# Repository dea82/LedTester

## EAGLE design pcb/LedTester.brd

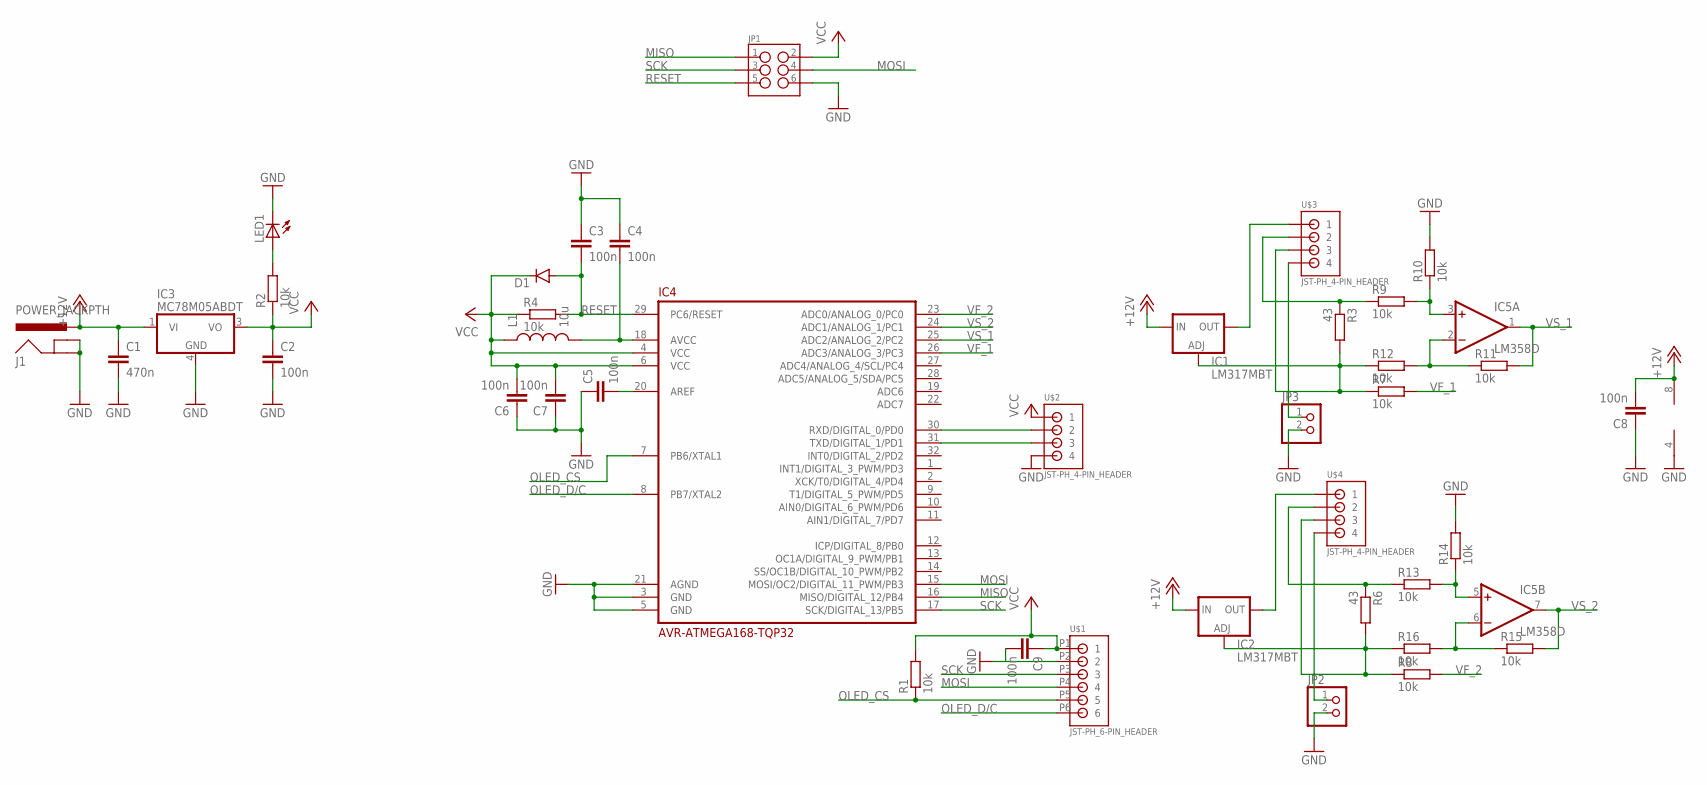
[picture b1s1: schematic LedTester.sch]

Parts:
C1: 470n; C0603
C2, C3, C4, C5, C6, C7, C8, C9: 100n; C0603
D1: DIODESOD; SOD-323
IC1, IC2: LM317MBT; TO220L1
IC3: MC78M05ABDT; DPACK_3
IC4: AVR-ATMEGA168-TQP32; QFP32
IC5: LM358D; SO08
J1: POWER_JACKPTH; POWER_JACK_PTH
JP1: M03X2SHROUD; 2X3-SHROUDED
JP2, JP3: PINHD-1X2; 1X02
L1: 10u; 0603
LED1: LEDCHIP-LED0603; CHIP-LED0603
R1, R2, R4, R7, R8, R9, R10, R11, R12, R13, R14, R15, R16: 10k; R0603
R3, R6: 43; R0603
U$1: JST-PH_6-PIN_HEADER; JST_B6B-PH_HEADER
U$2, U$3, U$4: JST-PH_4-PIN_HEADER; JST_B4B-PH_HEADER

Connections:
+12V: C1.1, C8.2, IC1.3 (IN), IC2.3 (IN), IC3.1 (VI), IC5.8 (V+), J1.PWR
GND: C1.2, C2.2, C3.1, C4.1, C5.1, C6.1, C7.1, C8.1, C9.2, IC3.4 (GND), IC4.3 (GND), IC4.5 (GND), IC4.21 (AGND), IC5.4 (V-), J1.GND, J1.GNDBREAK, JP1.6, JP2.2, JP3.2, LED1.C, R10.2, R14.2, U$1.P2 (2), U$2.P4 (4)
MISO: IC4.16 (MISO/DIGITAL_12/PB4), JP1.1
MOSI: IC4.15 (MOSI/OC2/DIGITAL_11_PWM/PB3), JP1.4, U$1.P4 (4)
unnamed: C5.2, IC4.20 (AREF)
unnamed: IC1.2 (OUT), U$3.P1 (1)
unnamed: C4.2, IC4.18 (AVCC), L1.2
unnamed: R3.1, R9.1, U$3.P2 (2)
unnamed: IC1.1 (ADJ), R3.2, R7.1, R12.1, U$3.P3 (3)
unnamed: IC2.2 (OUT), U$4.P1 (1)
unnamed: R6.1, R13.1, U$4.P2 (2)
unnamed: IC2.1 (ADJ), R6.2, R8.1, R16.1, U$4.P3 (3)
unnamed: LED1.A, R2.2
unnamed: IC4.30 (RXD/DIGITAL_0/PD0), U$2.P2 (2)
unnamed: IC4.31 (TXD/DIGITAL_1/PD1), U$2.P3 (3)
unnamed: IC5.2 (-IN), R11.1, R12.2
unnamed: IC5.3 (+IN), R9.2, R10.1
unnamed: IC5.6 (-IN), R15.1, R16.2
unnamed: IC5.5 (+IN), R13.2, R14.1
unnamed: JP3.1, U$3.P4 (4)
unnamed: JP2.1, U$4.P4 (4)
OLED_CS: IC4.7 (PB6/XTAL1), R1.1, U$1.P5 (5)
OLED_D/C: IC4.8 (PB7/XTAL2), U$1.P6 (6)
RESET: C3.2, D1.A, IC4.29 (PC6/RESET), JP1.5, R4.2
SCK: IC4.17 (SCK/DIGITAL_13/PB5), JP1.3, U$1.P3 (3)
VCC: C2.1, C6.2, C7.2, C9.1, D1.C, IC3.3 (VO), IC4.4 (VCC), IC4.6 (VCC), JP1.2, L1.1, R1.2, R2.1, R4.1, U$1.P1 (1), U$2.P1 (1)
VF_1: IC4.26 (ADC3/ANALOG_3/PC3), R7.2
VF_2: IC4.23 (ADC0/ANALOG_0/PC0), R8.2
VS_1: IC4.25 (ADC2/ANALOG_2/PC2), IC5.1 (OUT), R11.2
VS_2: IC4.24 (ADC1/ANALOG_1/PC1), IC5.7 (OUT), R15.2

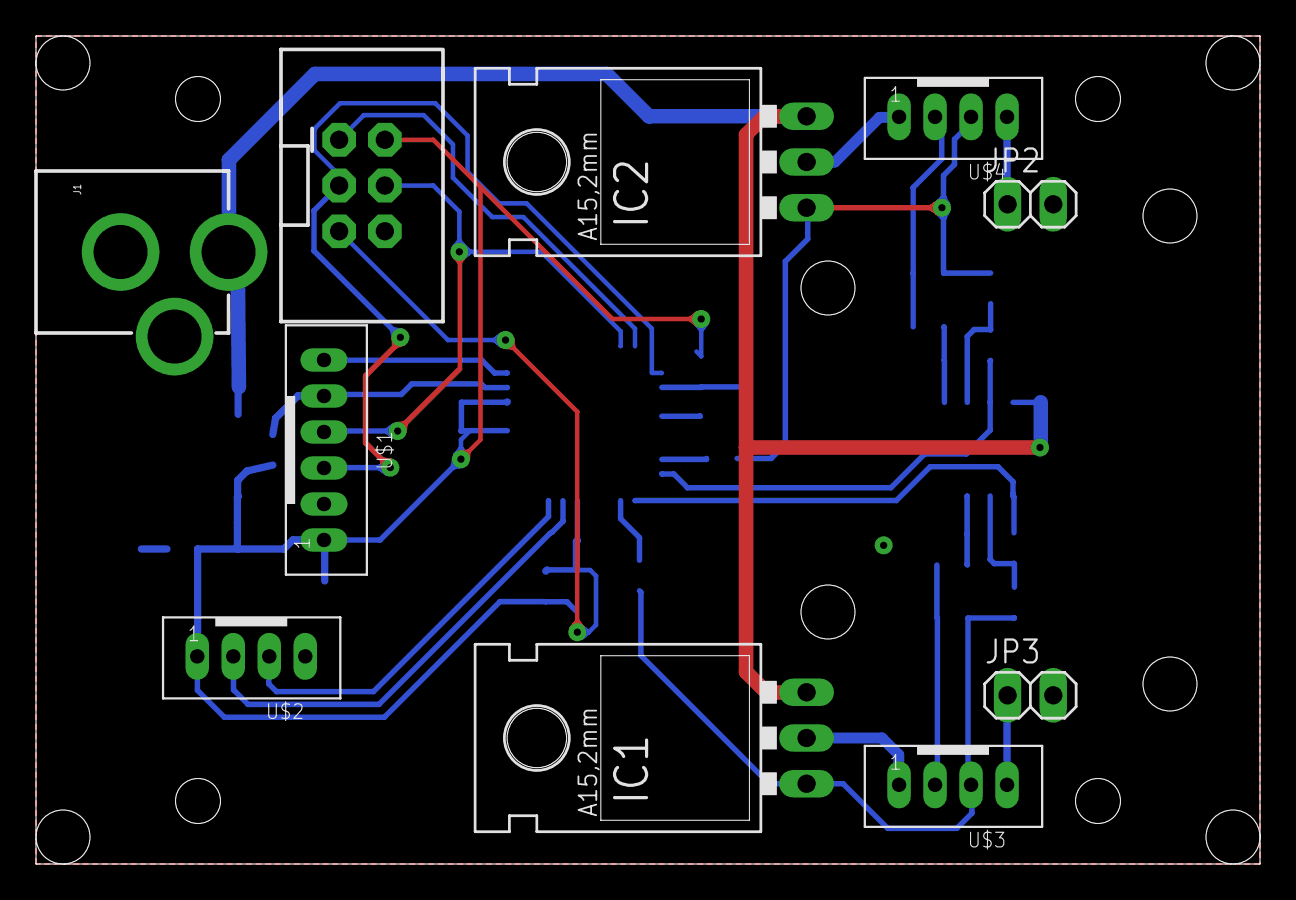
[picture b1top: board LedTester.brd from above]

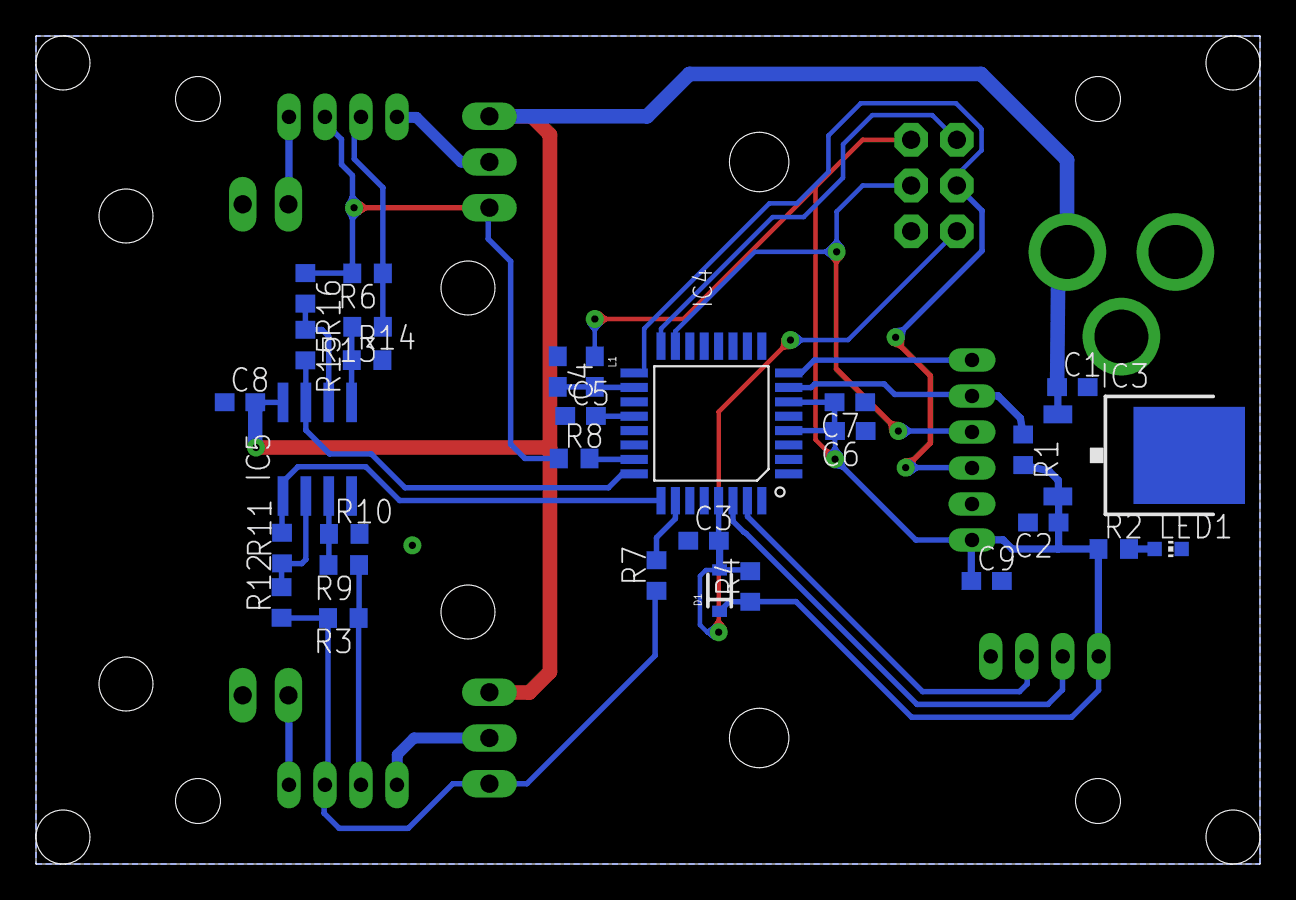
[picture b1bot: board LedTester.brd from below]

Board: 2 copper layers, 68.0 x 46.0 mm, 40 parts (30 on the bottom side), 30 nets.

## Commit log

2016-01-19 Create host program LedPlotter
2016-01-28 no message
2016-02-06 Create a first prototype of CMake
    Created a first version of a CMake script.
2016-02-06 Add project name in build script print out.
2016-02-07 Add general build script.
2017-02-05 Change build.sh for Jenkins
2017-02-05 Trying to remove init of modules

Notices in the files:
parts and their libraries:
SparkFun-DiscreteSemi: Licensing: Creative Commons ShareAlike 4.0 International - https://creativecommons.org/licenses/by-sa/4.0
